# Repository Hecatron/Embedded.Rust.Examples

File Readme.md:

# Readme

This is a series of examples / templates I've put together
for using Rust with an embedded platform such as the ESP32

## ESP32 Examples

The ESP32 Examples are based on the repo

  * https://github.com/MabezDev/xtensa-rust-quickstart

## TODO

https://nereux.blog/posts/esp32-ws2812-dino-light-2/

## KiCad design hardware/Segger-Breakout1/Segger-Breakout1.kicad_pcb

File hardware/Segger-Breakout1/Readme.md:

# Readme

Custom breakout board to allow the connection of a segger or RP2040 as a Jtag programmer

## RP2040

  * https://github.com/phdussud/pico-dirtyJtag

TDI 	GPIO16 	21
TDO 	GPIO17 	22
TCK 	GPIO18 	24
TMS 	GPIO19 	25
RST 	GPIO20 	26
TRST 	GPIO21 	27
DBG TX 	GPIO12 	16
DBG RX 	GPIO13 	17

https://github.com/kholia/xvc-pico/

TDI 	GPIO16
TDO 	GPIO17
TCK 	GPIO18
TMS 	GPIO19
GND 	Pin 23

https://github.com/tjko/tiny-picoprobe

VSYS
VBUS

TCK   GPIO2   4
TMS   GPIO3   5

DBG RX  GPIO4   6
DBG TX  GPIO5   7

https://github.com/rgrr/yapicoprobe

https://reltech.substack.com/p/getting-started-with-rust-on-a-raspberry
https://shop.segger.com/debug-trace-probes/debug-probes/adapters/flying-wire-adapter

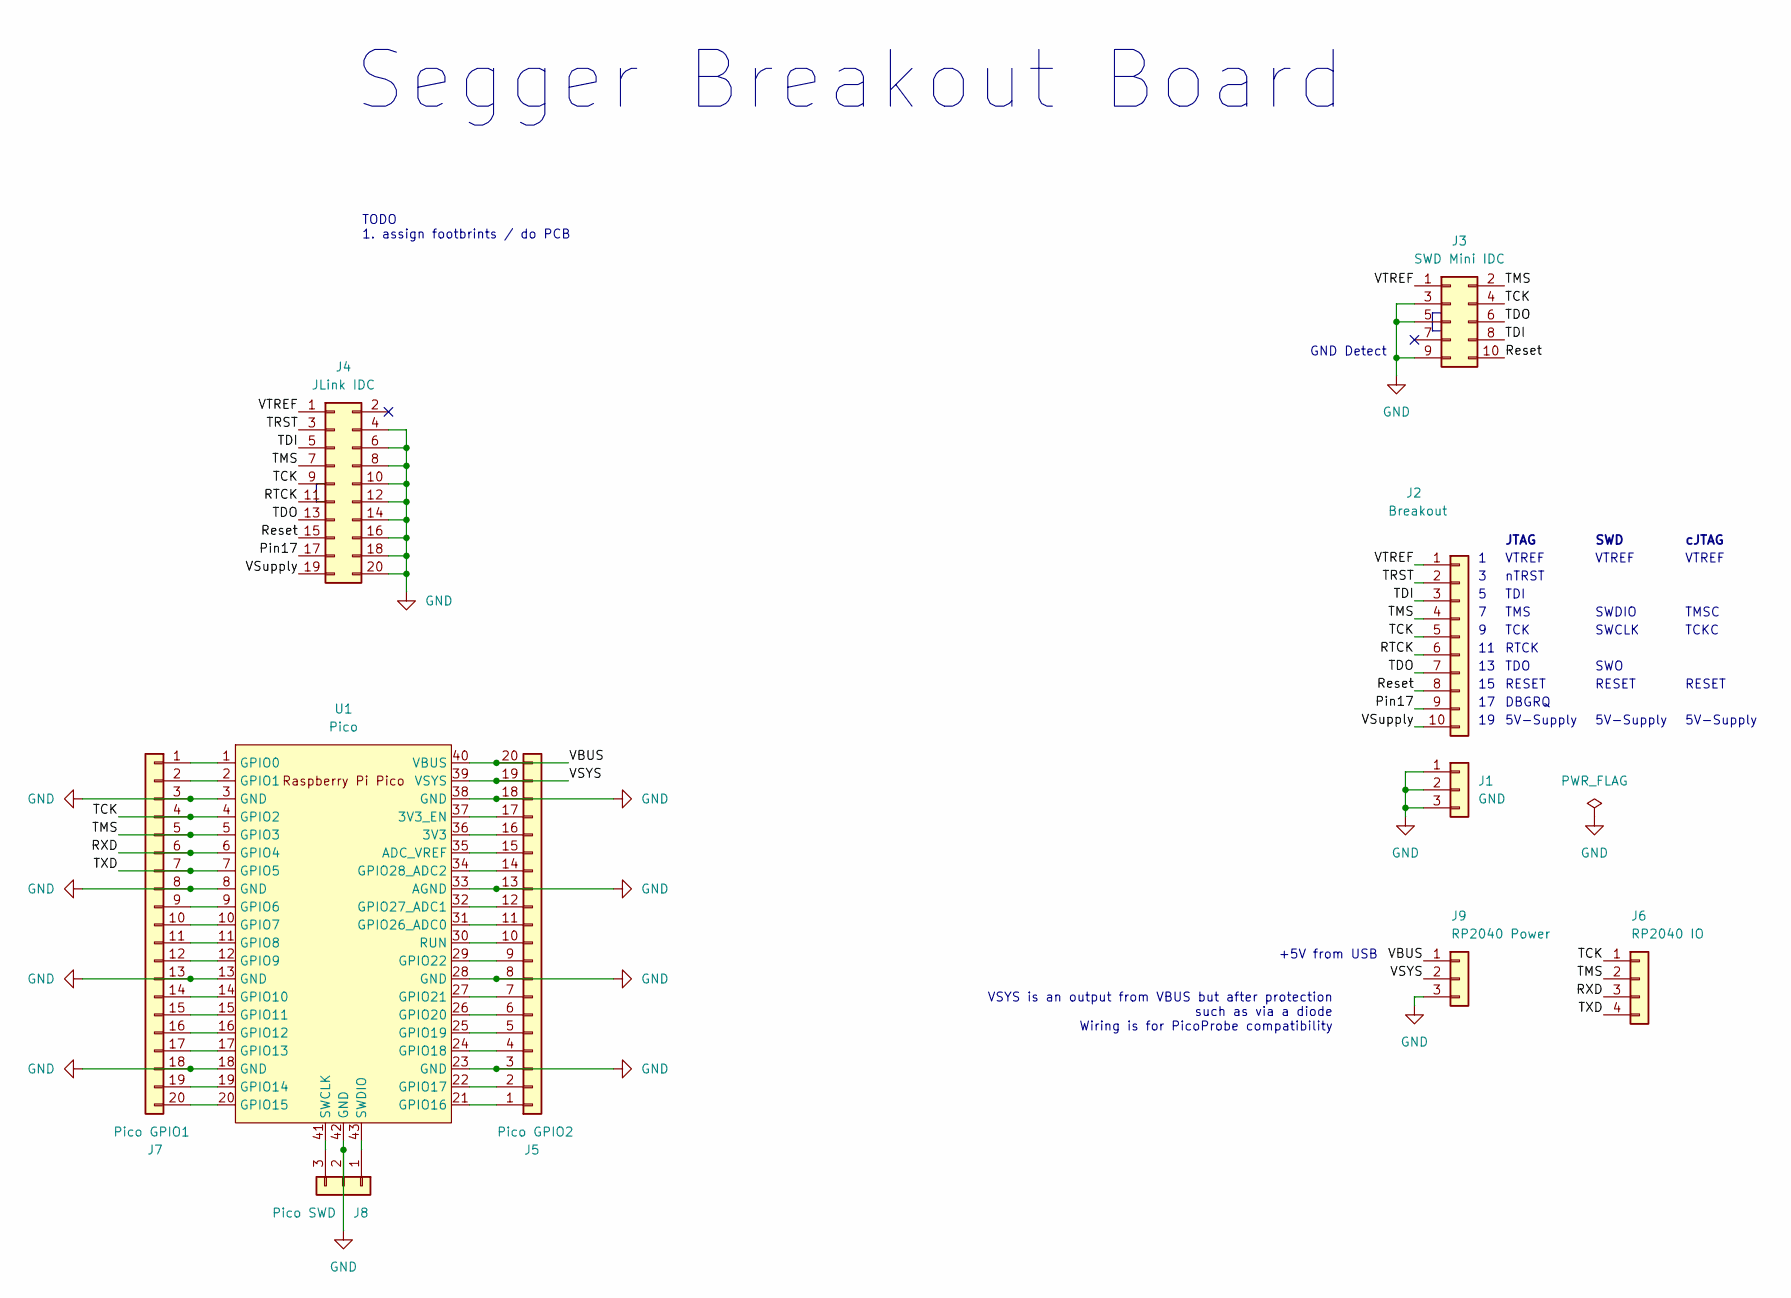
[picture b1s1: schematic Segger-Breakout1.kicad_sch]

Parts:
J1: GND; PinHeader_1x03_P2.54mm_Vertical
J2: Breakout; PinHeader_1x10_P2.54mm_Vertical
J3: SWD Mini IDC; PinHeader_2x05_P1.27mm_Vertical
J4: JLink IDC; IDC-Header_2x10_P2.54mm_Vertical
J5: Pico GPIO2; PinHeader_1x20_P2.54mm_Vertical
J6: RP2040 IO; PinHeader_1x04_P2.54mm_Vertical
J7: Pico GPIO1; PinHeader_1x20_P2.54mm_Vertical
J8: Pico SWD; PinHeader_1x03_P2.54mm_Vertical
J9: RP2040 Power; PinHeader_1x03_P2.54mm_Vertical
U1: Pico; RPi_Pico_SMD_TH

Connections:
/Pin17: J2.9, J4.17
/RTCK: J2.6, J4.11
/RXD: J6.3, J7.6, U1.6 (GPIO4)
/Reset: J2.8, J3.10, J4.15
/TCK: J2.5, J3.4, J4.9, J6.1, J7.4, U1.4 (GPIO2)
/TDI: J2.3, J3.8, J4.5
/TDO: J2.7, J3.6, J4.13
/TMS: J2.4, J3.2, J4.7, J6.2, J7.5, U1.5 (GPIO3)
/TRST: J2.2, J4.3
/TXD: J6.4, J7.7, U1.7 (GPIO5)
/VBUS: J5.20, J9.1, U1.40 (VBUS)
/VSYS: J5.19, J9.2, U1.39 (VSYS)
/VSupply: J2.10, J4.19
/VTREF: J2.1, J3.1, J4.1
GND: J1.1, J1.2, J1.3, J3.3, J3.5, J3.9, J4.4, J4.6, J4.8, J4.10, J4.12, J4.14, J4.16, J4.18, J4.20, J5.3, J5.8, J5.13, J5.18, J7.3, J7.8, J7.13, J7.18, J8.2, J9.3, U1.3 (GND), U1.8 (GND), U1.13 (GND), U1.18 (GND), U1.23 (GND), U1.28 (GND), U1.33 (AGND), U1.38 (GND), U1.42 (GND)
unnamed: J5.1, U1.21 (GPIO16)
unnamed: J5.2, U1.22 (GPIO17)
unnamed: J5.4, U1.24 (GPIO18)
unnamed: J5.5, U1.25 (GPIO19)
unnamed: J5.6, U1.26 (GPIO20)
unnamed: J5.7, U1.27 (GPIO21)
unnamed: J5.9, U1.29 (GPIO22)
unnamed: J5.10, U1.30 (RUN)
unnamed: J5.11, U1.31 (GPIO26_ADC0)
unnamed: J5.12, U1.32 (GPIO27_ADC1)
unnamed: J5.14, U1.34 (GPIO28_ADC2)
unnamed: J5.15, U1.35 (ADC_VREF)
unnamed: J5.16, U1.36 (3V3)
unnamed: J5.17, U1.37 (3V3_EN)
unnamed: J7.1, U1.1 (GPIO0)
unnamed: J7.2, U1.2 (GPIO1)
unnamed: J7.9, U1.9 (GPIO6)
unnamed: J7.10, U1.10 (GPIO7)
unnamed: J7.11, U1.11 (GPIO8)
unnamed: J7.12, U1.12 (GPIO9)
unnamed: J7.14, U1.14 (GPIO10)
unnamed: J7.15, U1.15 (GPIO11)
unnamed: J7.16, U1.16 (GPIO12)
unnamed: J7.17, U1.17 (GPIO13)
unnamed: J7.19, U1.19 (GPIO14)
unnamed: J7.20, U1.20 (GPIO15)
unnamed: J8.1, U1.43 (SWDIO)
unnamed: J8.3, U1.41 (SWCLK)

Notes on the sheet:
Segger Breakout Board
5V-Supply
+5V from USB
TCK
VTREF
RESET
TCKC
SWO
cJTAG
JTAG
RTCK
SWCLK
VSYS is an output from VBUS but after protection such as via a diode Wiring is for PicoProbe compatibility
nTRST
TDI
TMS
TDO
SWD
TODO 1. assign footbrints / do PCB
SWDIO
TMSC
GND Detect
DBGRQ

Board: 2 copper layers, 10 parts (0 on the bottom side), 43 nets, no tracks yet.

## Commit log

2021-02-06 code updates
2021-02-06 doc updates
2021-02-09 added cargo make
2021-02-09 added rust format
2021-02-09 update makefile
2021-02-09 update settings
2021-02-09 features update
2021-02-21 migrated the idf library to it's own repo
2021-10-26 update to docs
2021-10-26 docs updatet
2021-10-29 build script updates
2021-10-31 make file updates
2021-10-31 updated vscode tasks
2021-10-31 updated tasks list
2021-11-01 fixed build
2024-03-14 design updates
2025-03-26 up[da
